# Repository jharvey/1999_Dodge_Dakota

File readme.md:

#  1999 Dodge Dakota, based on rusEFI PROTEUS

A high-featured board compatible with [rusEFI](https://github.com/rusefi/rusefi) firmware.

# Goals 

- Run my 1999 Dodge Dakota with factory harness and equipment
- Run a sequential ignition, quad-VVT v12 engine (eight injectors, eight ignition, five hall sensors, four VVT actuators, single throttles)
- Easily manufactured sealed enclosure (all connectors mount in-plane)
- Extensible for knock sensing

# Hardware Features

## Microcontroller

- STM32F429ZG
    - 180 MHz ARM Cortex-M7
    - 1MB flash
    - 256 KB SRAM
    - LQFP144 package

- Also fully compatible with several STM32F7 parts, including the STM32F767ZI, used on v0.1 and v0.2, as well as STM32F429ZIT6.

## Connectors
Factory connector for most wiring with TE Connectivity AMPSEAL connector(s) for upgrades:

- 2x 35 pin connectors
    - Board: TE 776231-1 (black, right) and 776231-2 (white, left)
    - Plug: TE 776164-1 (black, right) and 776164-2 (white, left)
- 1x 23 pin connector
    - Board: TE 776228-1
    - Plug: TE 770680-1
- 770854-1 terminals    

## Connectivity

- 1 mbit/s CAN bus
- USB 2.0 full speed (12 mbit/s), on-board or wired to connector for sealed applications
- [10-pin, 1.27mm Cortex debug header](http://infocenter.arm.com/help/topic/com.arm.doc.faqs/attached/13634/cortex_debug_connectors.pdf)

## Outputs
TBD
- 16x 4A low-side drivers
- 12x 5v ignition (or general purpose) outputs
- Dual H-bridges for electronic throttle (also supports stepper idle valve!)
- 4x 12v 3A high-side outputs

## Inputs
TBD
- 11x Analog voltage inputs
- 4x Analog temperature (5v pullup) inputs
- 2x VR crank/cam/vehicle speed inputs
- 6x hall cam/crank or digital input

## Power Supply

- Full operation from 6-24v supply
- Limited operation from 4-6v
- Dual 5v sensor supplies, 150mA each, fully protected
- Dual protected 12v external sensor supply

## Extensibility

- 10-pin internal header for knock expansion board.  We aren't confident in any one knock sensing design yet, so it's most useful to be able to swap it out without replacing the whole ECU.

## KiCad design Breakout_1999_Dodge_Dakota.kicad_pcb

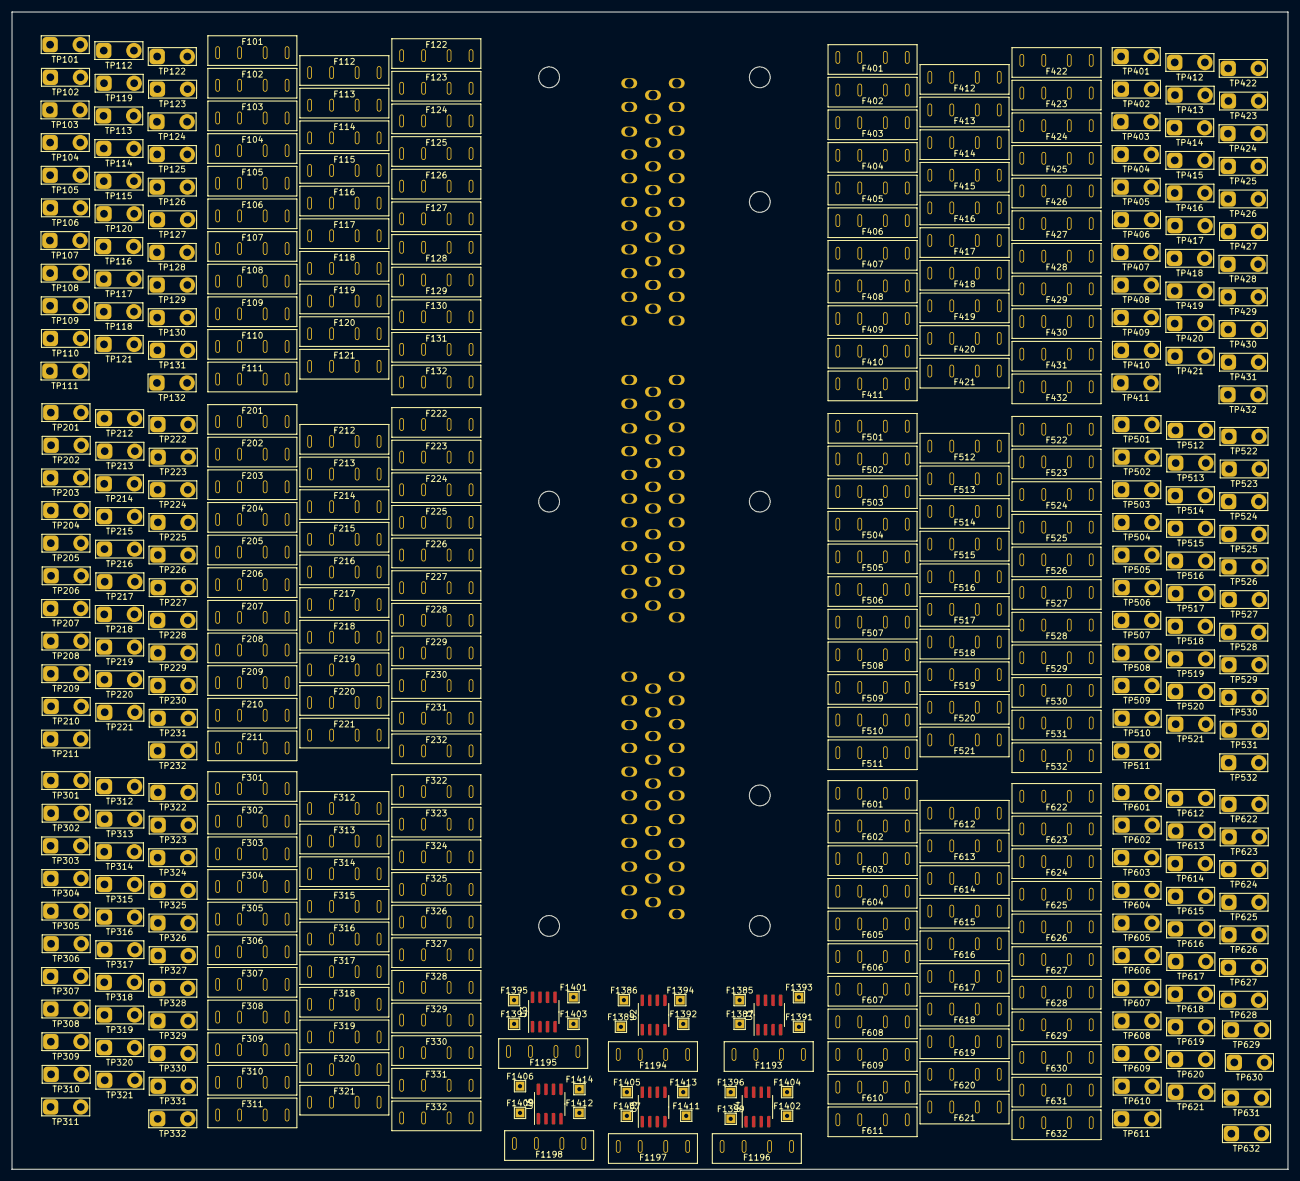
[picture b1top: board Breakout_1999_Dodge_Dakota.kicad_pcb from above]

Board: 4 copper layers, 215.0 x 195.0 mm, 421 parts (1 on the bottom side), 324 nets, no tracks yet.

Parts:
F101, F102, F103, F104, F105, F106, F107, F108, F109, F110, F111, F112, F113, F114, F115, F116, F117, F118, F119, F120, F121, F122, F123, F124, F125, F126, F127, F128, F129, F130, F131, F132, F201, F202, F203, F204, F205, F206, F207, F208, F209, F210, F211, F212, F213, F214, F215, F216, F217, F218, F219, F220, F221, F222, F223, F224, F225, F226, F227, F228, F229, F230, F231, F232, F301, F302, F303, F304, F305, F306, F307, F308, F309, F310, F311, F312, F313, F314, F315, F316, F317, F318, F319, F320, F321, F322, F323, F324, F325, F326, F327, F328, F329, F330, F331, F332, F401, F402, F403, F404, F405, F406, F407, F408, F409, F410, F411, F412, F413, F414, F415, F416, F417, F418, F419, F420, F421, F422, F423, F424, F425, F426, F427, F428, F429, F430, F431, F432, F501, F502, F503, F504, F505, F506, F507, F508, F509, F510, F511, F512, F513, F514, F515, F516, F517, F518, F519, F520, F521, F522, F523, F524, F525, F526, F527, F528, F529, F530, F531, F532, F601, F602, F603, F604, F605, F606, F607, F608, F609, F610, F611, F612, F613, F614, F615, F616, F617, F618, F619, F620, F621, F622, F623, F624, F625, F626, F627, F628, F629, F630, F631, F632, F1193, F1194, F1195, F1196, F1197, F1198: Fuse_Holder; LCSC_C2935870_Fuse_holder
F1385, F1386, F1387, F1389, F1391, F1392, F1393, F1394, F1395, F1396, F1397, F1399, F1401, F1402, F1403, F1404, F1405, F1406, F1407, F1409, F1411, F1412, F1413, F1414: Pig_Con; TestPoint_THTPad_1.5x1.5mm_Drill0.7mm
J1: Dodge_Con; 1999_Dodge_Connector_32x3cons
TP101, TP102, TP103, TP104, TP105, TP106, TP107, TP108, TP109, TP110, TP111, TP112, TP113, TP114, TP115, TP116, TP117, TP118, TP119, TP120, TP121, TP122, TP123, TP124, TP125, TP126, TP127, TP128, TP129, TP130, TP131, TP132, TP201, TP202, TP203, TP204, TP205, TP206, TP207, TP208, TP209, TP210, TP211, TP212, TP213, TP214, TP215, TP216, TP217, TP218, TP219, TP220, TP221, TP222, TP223, TP224, TP225, TP226, TP227, TP228, TP229, TP230, TP231, TP232, TP301, TP302, TP303, TP304, TP305, TP306, TP307, TP308, TP309, TP310, TP311, TP312, TP313, TP314, TP315, TP316, TP317, TP318, TP319, TP320, TP321, TP322, TP323, TP324, TP325, TP326, TP327, TP328, TP329, TP330, TP331, TP332, TP401, TP402, TP403, TP404, TP405, TP406, TP407, TP408, TP409, TP410, TP411, TP412, TP413, TP414, TP415, TP416, TP417, TP418, TP419, TP420, TP421, TP422, TP423, TP424, TP425, TP426, TP427, TP428, TP429, TP430, TP431, TP432, TP501, TP502, TP503, TP504, TP505, TP506, TP507, TP508, TP509, TP510, TP511, TP512, TP513, TP514, TP515, TP516, TP517, TP518, TP519, TP520, TP521, TP522, TP523, TP524, TP525, TP526, TP527, TP528, TP529, TP530, TP531, TP532, TP601, TP602, TP603, TP604, TP605, TP606, TP607, TP608, TP609, TP610, TP611, TP612, TP613, TP614, TP615, TP616, TP617, TP618, TP619, TP620, TP621, TP622, TP623, TP624, TP625, TP626, TP627, TP628, TP629, TP630, TP631, TP632: TestPoint_2Pole; TestPoint_2Pads_Pitch5.08mm_Drill1.3mm
U1, U2, U3, U4, U5, U6: ACS712xLCTR-20A; SOIC-8_3.9x4.9mm_P1.27mm

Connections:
unnamed: F101.1, TP101.1, TP101.2
unnamed: F101.2, F401.1, J1.c1-1 (Pin_1)
unnamed: F102.1, TP102.1, TP102.2
unnamed: F102.2, F402.1, J1.c1-2 (Pin_2)
unnamed: F103.1, TP103.1, TP103.2
unnamed: F103.2, F403.1, J1.c1-3 (Pin_3)
unnamed: F104.1, TP104.1, TP104.2
unnamed: F104.2, F404.1, J1.c1-4 (Pin_4)
unnamed: F105.1, TP105.1, TP105.2
unnamed: F105.2, F405.1, J1.c1-5 (Pin_5)
unnamed: F106.1, TP106.1, TP106.2
unnamed: F106.2, F406.1, J1.c1-6 (Pin_6)
unnamed: F107.1, TP107.1, TP107.2
unnamed: F107.2, F407.1, J1.c1-7 (Pin_7)
unnamed: F108.1, TP108.1, TP108.2
unnamed: F108.2, F408.1, J1.c1-8 (Pin_8)
unnamed: F109.1, TP109.1, TP109.2
unnamed: F109.2, F409.1, J1.c1-9 (Pin_9)
unnamed: F110.1, TP110.1, TP110.2
unnamed: F110.2, F410.1, J1.c1-10 (Pin_10)
unnamed: F111.1, TP111.1, TP111.2
unnamed: F111.2, F411.1, J1.c1-11 (Pin_11)
unnamed: F112.1, TP112.1, TP112.2
unnamed: F112.2, F412.1, J1.c1-12 (Pin_12)
unnamed: F113.1, TP113.1, TP113.2
unnamed: F113.2, F413.1, J1.c1-13 (Pin_13)
unnamed: F114.1, TP114.1, TP114.2
unnamed: F114.2, F414.1, J1.c1-14 (Pin_14)
unnamed: F115.1, TP115.1, TP115.2
unnamed: F115.2, F415.1, J1.c1-15 (Pin_15)
unnamed: F116.1, TP116.1, TP116.2
unnamed: F116.2, F416.1, J1.c1-16 (Pin_16)
unnamed: F117.1, TP117.1, TP117.2
unnamed: F117.2, F417.1, J1.c1-17 (Pin_17)
unnamed: F118.1, TP118.1, TP118.2
unnamed: F118.2, F418.1, J1.c1-18 (Pin_18)
unnamed: F119.1, TP119.1, TP119.2
unnamed: F119.2, F419.1, J1.c1-19 (Pin_19)
unnamed: F120.1, TP120.1, TP120.2
unnamed: F120.2, F420.1, J1.c1-20 (Pin_20)
unnamed: F121.1, TP121.1, TP121.2
unnamed: F121.2, F421.1, J1.c1-21 (Pin_21)
unnamed: F122.1, TP122.1, TP122.2
unnamed: F122.2, F422.1, J1.c1-22 (Pin_22)
unnamed: F123.1, TP123.1, TP123.2
unnamed: F123.2, F423.1, J1.c1-23 (Pin_23)
unnamed: F124.1, TP124.1, TP124.2
unnamed: F124.2, F424.1, J1.c1-24 (Pin_24)
unnamed: F125.1, TP125.1, TP125.2
unnamed: F125.2, F425.1, J1.c1-25 (Pin_25)
unnamed: F126.1, TP126.1, TP126.2
unnamed: F126.2, F426.1, J1.c1-26 (Pin_26)
unnamed: F127.1, TP127.1, TP127.2
unnamed: F127.2, F427.1, J1.c1-27 (Pin_27)
unnamed: F128.1, TP128.1, TP128.2
unnamed: F128.2, F428.1, J1.c1-28 (Pin_28)
unnamed: F129.1, TP129.1, TP129.2
unnamed: F129.2, F429.1, J1.c1-29 (Pin_29)
unnamed: F130.1, TP130.1, TP130.2
unnamed: F130.2, F430.1, J1.c1-30 (Pin_30)
unnamed: F131.1, TP131.1, TP131.2
unnamed: F131.2, F431.1, J1.c1-31 (Pin_31)
unnamed: F132.1, TP132.1, TP132.2
unnamed: F132.2, F432.1, J1.c1-32 (Pin_32)
unnamed: F201.1, TP201.1, TP201.2
unnamed: F201.2, F501.1, J1.c2-1 (Pin_1)
unnamed: F202.1, TP202.1, TP202.2
unnamed: F202.2, F502.1, J1.c2-2 (Pin_2)
unnamed: F203.1, TP203.1, TP203.2
unnamed: F203.2, F503.1, J1.c2-3 (Pin_3)
unnamed: F204.1, TP204.1, TP204.2
unnamed: F204.2, F504.1, J1.c2-4 (Pin_4)
unnamed: F205.1, TP205.1, TP205.2
unnamed: F205.2, F505.1, J1.c2-5 (Pin_5)
unnamed: F206.1, TP206.1, TP206.2
unnamed: F206.2, F506.1, J1.c2-6 (Pin_6)
unnamed: F207.1, TP207.1, TP207.2
unnamed: F207.2, F507.1, J1.c2-7 (Pin_7)
unnamed: F208.1, TP208.1, TP208.2
unnamed: F208.2, F508.1, J1.c2-8 (Pin_8)
unnamed: F209.1, TP209.1, TP209.2
unnamed: F209.2, F509.1, J1.c2-9 (Pin_9)
unnamed: F210.1, TP210.1, TP210.2
unnamed: F210.2, F510.1, J1.c2-10 (Pin_10)
unnamed: F211.1, TP211.1, TP211.2
unnamed: F211.2, F511.1, J1.c2-11 (Pin_11)
unnamed: F212.1, TP212.1, TP212.2
unnamed: F212.2, F512.1, J1.c2-12 (Pin_12)
unnamed: F213.1, TP213.1, TP213.2
unnamed: F213.2, F513.1, J1.c2-13 (Pin_13)
unnamed: F214.1, TP214.1, TP214.2
unnamed: F214.2, F514.1, J1.c2-14 (Pin_14)
unnamed: F215.1, TP215.1, TP215.2
unnamed: F215.2, F515.1, J1.c2-15 (Pin_15)
unnamed: F216.1, TP216.1, TP216.2
unnamed: F216.2, F516.1, J1.c2-16 (Pin_16)
unnamed: F217.1, TP217.1, TP217.2
unnamed: F217.2, F517.1, J1.c2-17 (Pin_17)
unnamed: F218.1, TP218.1, TP218.2
unnamed: F218.2, F518.1, J1.c2-18 (Pin_18)
unnamed: F219.1, TP219.1, TP219.2
unnamed: F219.2, F519.1, J1.c2-19 (Pin_19)
unnamed: F220.1, TP220.1, TP220.2
unnamed: F220.2, F520.1, J1.c2-20 (Pin_20)
unnamed: F221.1, TP221.1, TP221.2
unnamed: F221.2, F521.1, J1.c2-21 (Pin_21)
unnamed: F222.1, TP222.1, TP222.2
unnamed: F222.2, F522.1, J1.c2-22 (Pin_22)
unnamed: F223.1, TP223.1, TP223.2
unnamed: F223.2, F523.1, J1.c2-23 (Pin_23)
unnamed: F224.1, TP224.1, TP224.2
unnamed: F224.2, F524.1, J1.c2-24 (Pin_24)
unnamed: F225.1, TP225.1, TP225.2
unnamed: F225.2, F525.1, J1.c2-25 (Pin_25)
unnamed: F226.1, TP226.1, TP226.2
unnamed: F226.2, F526.1, J1.c2-26 (Pin_26)
unnamed: F227.1, TP227.1, TP227.2
unnamed: F227.2, F527.1, J1.c2-27 (Pin_27)
unnamed: F228.1, TP228.1, TP228.2
unnamed: F228.2, F528.1, J1.c2-28 (Pin_28)
unnamed: F229.1, TP229.1, TP229.2
unnamed: F229.2, F529.1, J1.c2-29 (Pin_29)
unnamed: F230.1, TP230.1, TP230.2
unnamed: F230.2, F530.1, J1.c2-30 (Pin_30)
unnamed: F231.1, TP231.1, TP231.2
unnamed: F231.2, F531.1, J1.c2-31 (Pin_31)
unnamed: F232.1, TP232.1, TP232.2
unnamed: F232.2, F532.1, J1.c2-32 (Pin_32)
unnamed: F301.1, TP301.1, TP301.2
unnamed: F301.2, F601.1, J1.c3-1 (Pin_1)
unnamed: F302.1, TP302.1, TP302.2
unnamed: F302.2, F602.1, J1.c3-2 (Pin_2)
unnamed: F303.1, TP303.1, TP303.2
unnamed: F303.2, F603.1, J1.c3-3 (Pin_3)
unnamed: F304.1, TP304.1, TP304.2
unnamed: F304.2, F604.1, J1.c3-4 (Pin_4)
unnamed: F305.1, TP305.1, TP305.2
unnamed: F305.2, F605.1, J1.c3-5 (Pin_5)
unnamed: F306.1, TP306.1, TP306.2
unnamed: F306.2, F606.1, J1.c3-6 (Pin_6)
unnamed: F307.1, TP307.1, TP307.2
unnamed: F307.2, F607.1, J1.c3-7 (Pin_7)
unnamed: F308.1, TP308.1, TP308.2
unnamed: F308.2, F608.1, J1.c3-8 (Pin_8)
unnamed: F309.1, TP309.1, TP309.2
unnamed: F309.2, F609.1, J1.c3-9 (Pin_9)
unnamed: F310.1, TP310.1, TP310.2
unnamed: F310.2, F610.1, J1.c3-10 (Pin_10)
unnamed: F311.1, TP311.1, TP311.2
unnamed: F311.2, F611.1, J1.c3-11 (Pin_11)
unnamed: F312.1, TP312.1, TP312.2
unnamed: F312.2, F612.1, J1.c3-12 (Pin_12)
unnamed: F313.1, TP313.1, TP313.2
unnamed: F313.2, F613.1, J1.c3-13 (Pin_13)
unnamed: F314.1, TP314.1, TP314.2
unnamed: F314.2, F614.1, J1.c3-14 (Pin_14)
unnamed: F315.1, TP315.1, TP315.2
unnamed: F315.2, F615.1, J1.c3-15 (Pin_15)
unnamed: F316.1, TP316.1, TP316.2
unnamed: F316.2, F616.1, J1.c3-16 (Pin_16)
unnamed: F317.1, TP317.1, TP317.2
unnamed: F317.2, F617.1, J1.c3-17 (Pin_17)
unnamed: F318.1, TP318.1, TP318.2
unnamed: F318.2, F618.1, J1.c3-18 (Pin_18)
unnamed: F319.1, TP319.1, TP319.2
unnamed: F319.2, F619.1, J1.c3-19 (Pin_19)
unnamed: F320.1, TP320.1, TP320.2
unnamed: F320.2, F620.1, J1.c3-20 (Pin_20)
unnamed: F321.1, TP321.1, TP321.2
unnamed: F321.2, F621.1, J1.c3-21 (Pin_21)
unnamed: F322.1, TP322.1, TP322.2
unnamed: F322.2, F622.1, J1.c3-22 (Pin_22)
unnamed: F323.1, TP323.1, TP323.2
unnamed: F323.2, F623.1, J1.c3-23 (Pin_23)
unnamed: F324.1, TP324.1, TP324.2
unnamed: F324.2, F624.1, J1.c3-24 (Pin_24)
unnamed: F325.1, TP325.1, TP325.2
unnamed: F325.2, F625.1, J1.c3-25 (Pin_25)
unnamed: F326.1, TP326.1, TP326.2
unnamed: F326.2, F626.1, J1.c3-26 (Pin_26)
unnamed: F327.1, TP327.1, TP327.2
unnamed: F327.2, F627.1, J1.c3-27 (Pin_27)
unnamed: F328.1, TP328.1, TP328.2
unnamed: F328.2, F628.1, J1.c3-28 (Pin_28)
unnamed: F329.1, TP329.1, TP329.2
unnamed: F329.2, F629.1, J1.c3-29 (Pin_29)
unnamed: F330.1, TP330.1, TP330.2
unnamed: F330.2, F630.1, J1.c3-30 (Pin_30)
unnamed: F331.1, TP331.1, TP331.2
unnamed: F331.2, F631.1, J1.c3-31 (Pin_31)
unnamed: F332.1, TP332.1, TP332.2
unnamed: F332.2, F632.1, J1.c3-32 (Pin_32)
unnamed: F401.2, TP401.1, TP401.2
unnamed: F402.2, TP402.1, TP402.2
unnamed: F403.2, TP403.1, TP403.2
unnamed: F404.2, TP404.1, TP404.2
unnamed: F405.2, TP405.1, TP405.2
unnamed: F406.2, TP406.1, TP406.2
unnamed: F407.2, TP407.1, TP407.2
unnamed: F408.2, TP408.1, TP408.2
unnamed: F409.2, TP409.1, TP409.2
unnamed: F410.2, TP410.1, TP410.2
unnamed: F411.2, TP411.1, TP411.2
unnamed: F412.2, TP412.1, TP412.2
unnamed: F413.2, TP413.1, TP413.2
unnamed: F414.2, TP414.1, TP414.2
unnamed: F415.2, TP415.1, TP415.2
unnamed: F416.2, TP416.1, TP416.2
unnamed: F417.2, TP417.1, TP417.2
unnamed: F418.2, TP418.1, TP418.2
unnamed: F419.2, TP419.1, TP419.2
unnamed: F420.2, TP420.1, TP420.2
unnamed: F421.2, TP421.1, TP421.2
unnamed: F422.2, TP422.1, TP422.2
unnamed: F423.2, TP423.1, TP423.2
unnamed: F424.2, TP424.1, TP424.2
unnamed: F425.2, TP425.1, TP425.2
unnamed: F426.2, TP426.1, TP426.2
unnamed: F427.2, TP427.1, TP427.2
unnamed: F428.2, TP428.1, TP428.2
unnamed: F429.2, TP429.1, TP429.2
unnamed: F430.2, TP430.1, TP430.2
unnamed: F431.2, TP431.1, TP431.2
unnamed: F432.2, TP432.1, TP432.2
unnamed: F501.2, TP501.1, TP501.2
unnamed: F502.2, TP502.1, TP502.2
unnamed: F503.2, TP503.1, TP503.2
unnamed: F504.2, TP504.1, TP504.2
unnamed: F505.2, TP505.1, TP505.2
unnamed: F506.2, TP506.1, TP506.2
unnamed: F507.2, TP507.1, TP507.2
unnamed: F508.2, TP508.1, TP508.2
unnamed: F509.2, TP509.1, TP509.2
unnamed: F510.2, TP510.1, TP510.2
unnamed: F511.2, TP511.1, TP511.2
unnamed: F512.2, TP512.1, TP512.2
unnamed: F513.2, TP513.1, TP513.2
unnamed: F514.2, TP514.1, TP514.2
unnamed: F515.2, TP515.1, TP515.2
unnamed: F516.2, TP516.1, TP516.2
unnamed: F517.2, TP517.1, TP517.2
unnamed: F518.2, TP518.1, TP518.2
unnamed: F519.2, TP519.1, TP519.2
unnamed: F520.2, TP520.1, TP520.2
unnamed: F521.2, TP521.1, TP521.2
unnamed: F522.2, TP522.1, TP522.2
unnamed: F523.2, TP523.1, TP523.2
unnamed: F524.2, TP524.1, TP524.2
unnamed: F525.2, TP525.1, TP525.2
unnamed: F526.2, TP526.1, TP526.2
unnamed: F527.2, TP527.1, TP527.2
unnamed: F528.2, TP528.1, TP528.2
unnamed: F529.2, TP529.1, TP529.2
unnamed: F530.2, TP530.1, TP530.2
unnamed: F531.2, TP531.1, TP531.2
unnamed: F532.2, TP532.1, TP532.2
unnamed: F601.2, TP601.1, TP601.2
unnamed: F602.2, TP602.1, TP602.2
unnamed: F603.2, TP603.1, TP603.2
unnamed: F604.2, TP604.1, TP604.2
unnamed: F605.2, TP605.1, TP605.2
unnamed: F606.2, TP606.1, TP606.2
unnamed: F607.2, TP607.1, TP607.2
unnamed: F608.2, TP608.1, TP608.2
unnamed: F609.2, TP609.1, TP609.2
unnamed: F610.2, TP610.1, TP610.2
unnamed: F611.2, TP611.1, TP611.2
unnamed: F612.2, TP612.1, TP612.2
unnamed: F613.2, TP613.1, TP613.2
unnamed: F614.2, TP614.1, TP614.2
unnamed: F615.2, TP615.1, TP615.2
unnamed: F616.2, TP616.1, TP616.2
unnamed: F617.2, TP617.1, TP617.2
unnamed: F618.2, TP618.1, TP618.2
unnamed: F619.2, TP619.1, TP619.2
unnamed: F620.2, TP620.1, TP620.2
unnamed: F621.2, TP621.1, TP621.2
unnamed: F622.2, TP622.1, TP622.2
unnamed: F623.2, TP623.1, TP623.2
unnamed: F624.2, TP624.1, TP624.2
unnamed: F625.2, TP625.1, TP625.2
unnamed: F626.2, TP626.1, TP626.2
unnamed: F627.2, TP627.1, TP627.2
unnamed: F628.2, TP628.1, TP628.2
unnamed: F629.2, TP629.1, TP629.2
unnamed: F630.2, TP630.1, TP630.2
unnamed: F631.2, TP631.1, TP631.2
unnamed: F632.2, TP632.1, TP632.2
unnamed: F1193.1, U1.3 (IP-), U1.4 (IP-)
unnamed: F1193.2, U1.1 (IP+), U1.2 (IP+)
unnamed: F1194.1, U2.3 (IP-), U2.4 (IP-)
unnamed: F1194.2, U2.1 (IP+), U2.2 (IP+)
unnamed: F1195.1, U3.3 (IP-), U3.4 (IP-)
unnamed: F1195.2, U3.1 (IP+), U3.2 (IP+)
unnamed: F1196.1, U4.3 (IP-), U4.4 (IP-)
unnamed: F1196.2, U4.1 (IP+), U4.2 (IP+)
unnamed: F1197.1, U5.3 (IP-), U5.4 (IP-)
unnamed: F1197.2, U5.1 (IP+), U5.2 (IP+)
unnamed: F1198.1, U6.3 (IP-), U6.4 (IP-)
unnamed: F1198.2, U6.1 (IP+), U6.2 (IP+)
unnamed: F1385.1, U1.8 (VCC)
unnamed: F1386.1, U2.8 (VCC)
unnamed: F1387.1, U1.7 (VIOUT)
unnamed: F1389.1, U2.7 (VIOUT)
unnamed: F1391.1, U1.6 (FILTER)
unnamed: F1392.1, U2.6 (FILTER)
unnamed: F1393.1, U1.5 (GND)
unnamed: F1394.1, U2.5 (GND)
unnamed: F1395.1, U3.8 (VCC)
unnamed: F1396.1, U4.8 (VCC)
unnamed: F1397.1, U3.7 (VIOUT)
unnamed: F1399.1, U4.7 (VIOUT)
unnamed: F1401.1, U3.6 (FILTER)
unnamed: F1402.1, U4.6 (FILTER)
unnamed: F1403.1, U3.5 (GND)
unnamed: F1404.1, U4.5 (GND)
unnamed: F1405.1, U5.8 (VCC)
unnamed: F1406.1, U6.8 (VCC)
unnamed: F1407.1, U5.7 (VIOUT)
unnamed: F1409.1, U6.7 (VIOUT)
unnamed: F1411.1, U5.6 (FILTER)
unnamed: F1412.1, U6.6 (FILTER)
unnamed: F1413.1, U5.5 (GND)
unnamed: F1414.1, U6.5 (GND)

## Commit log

2023-08-13 Updated symbols to KC7 links for C17, C1001, D1, D2, FB1501, JP1201, 3.3V Updated symbols to KC7 links and made minor adjustments to wires for JP1 and JP2 Deleted unused rescue files.
2023-08-13 File names changed / moved to folders. Updated file names to 1999_Dodge_Dakota Moved files footprints and symbols into a folder
2023-08-13 Removed extra file
2023-08-13 updated ignore list
2023-08-13 updated ignore list again, this time it may actually ignore the file.
2023-08-19 Draft breakout board check in.
2023-08-19 Another draft check in. Deleted unused "export" files.
2023-08-20 Draft commit, mostly routed, silk screen needs work. Passes ERC and DRC
2023-08-20 Breakout V0.1 Checked in.
2023-09-06 Added Pictures
2023-09-06 Added / modified pictures
2023-09-07 Made slight changes to screw holes and 3D model per first built. Moved holes 0.5mm.
2023-09-08 Added URL to connector 3D model.
